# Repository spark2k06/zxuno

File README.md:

# loader128k y 128sna2rom

Cargador de "ROMs" para ZXUno a partir snapshots de 128K, para utilizar desde el menú del firmware. 

Por un lado tenemos el cargador loader128k, que se autocopia en la VRAM para despues pasar el control al mismo. 

Desde la VRAM se mueven todos los bloques de 16Kb al lugar que les corresponde, se restauran los registros y por último se 

pasa el control al PC del Snapshot.

128sna2rom por su parte se utiliza para crear la "ROM" parcheando datos de loader128k.

Idea desarrollada a partir del siguiente hilo con ayuda de Antonio Villena y el emulador ZEsarUX de Cesar Hernández:

http://www.zxuno.com/forum/viewtopic.php?f=12&t=530

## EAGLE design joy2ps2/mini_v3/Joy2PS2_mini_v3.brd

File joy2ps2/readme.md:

# JOY2PS2 Release 7

[Documentación en Español](https://dokuwiki.aitorgomez.net/joy2ps2_es)

[Documentation in English](https://dokuwiki.aitorgomez.net/joy2ps2_en)

## Release 1 Demo

## Development and history of the project

http://www.zxuno.com/forum/viewtopic.php?f=63&t=1508

http://www.zxuno.com/forum/viewtopic.php?f=63&t=1507

http://www.zxuno.com/forum/viewtopic.php?f=63&t=1500

http://www.zxuno.com/forum/viewtopic.php?f=63&t=796

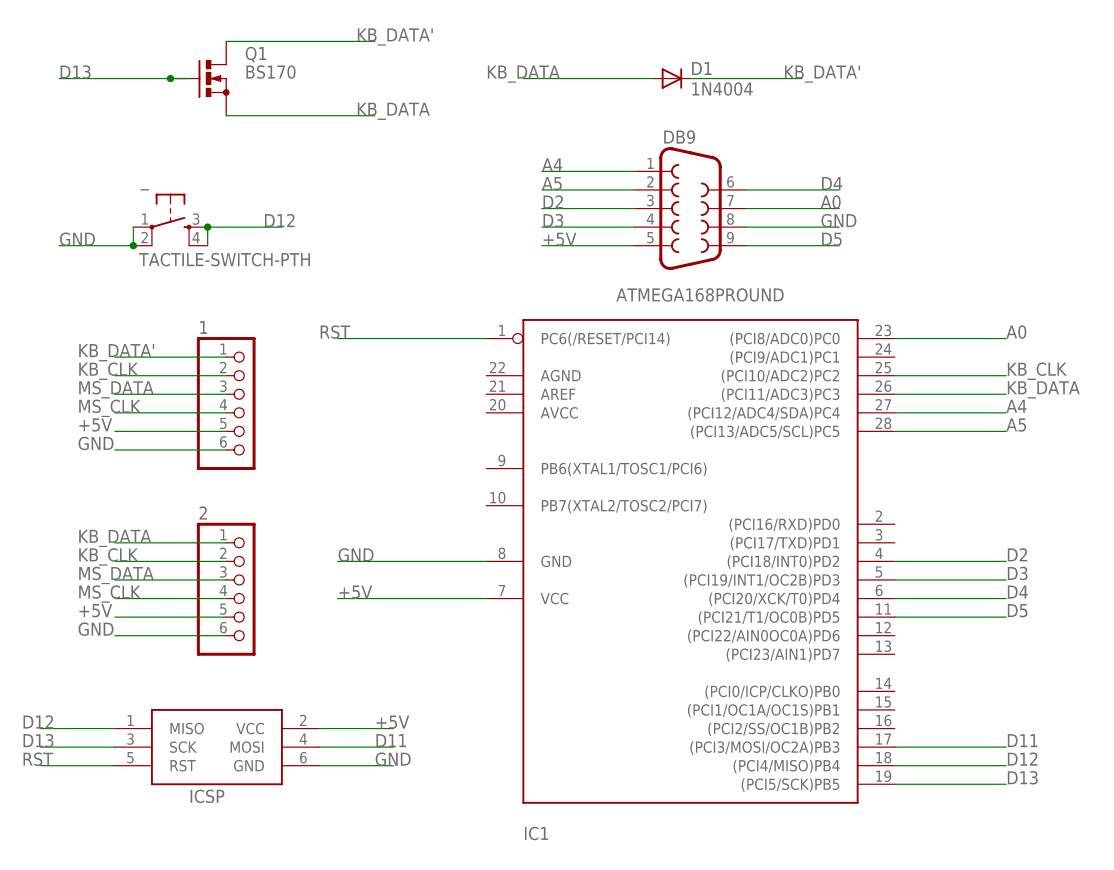
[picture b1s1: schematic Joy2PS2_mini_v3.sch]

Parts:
1, 2: PINHD-1X6; 1X06
D1: 1N4004; DO41-10
DB9: DB9MALE; DB9_MALE
IC1: ATMEGA168PROUND; DIL28-3-ROUND
ICSP: AVRISP-6; AVRISP
Q1: BS170; SOT54E
_: TACTILE-SWITCH-PTH; TAC-SWITCH-PTH

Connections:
+5V: 1.5, 2.5, DB9.5, IC1.7 (VCC), ICSP.2 (VCC)
A0: DB9.7, IC1.23 ((PCI8/ADC0)PC0)
A4: DB9.1, IC1.27 ((PCI12/ADC4/SDA)PC4)
A5: DB9.2, IC1.28 ((PCI13/ADC5/SCL)PC5)
D2: DB9.3, IC1.4 ((PCI18/INT0)PD2)
D3: DB9.4, IC1.5 ((PCI19/INT1/OC2B)PD3)
D4: DB9.6, IC1.6 ((PCI20/XCK/T0)PD4)
D5: DB9.9, IC1.11 ((PCI21/T1/OC0B)PD5)
D11: IC1.17 ((PCI3/MOSI/OC2A)PB3), ICSP.4 (MOSI)
D12: IC1.18 ((PCI4/MISO)PB4), ICSP.1 (MISO), _.3, _.4
D13: IC1.19 ((PCI5/SCK)PB5), ICSP.3 (SCK), Q1.G
GND: 1.6, 2.6, DB9.8, IC1.8 (GND), ICSP.6 (GND), _.1, _.2
KB_CLK: 1.2, 2.2, IC1.25 ((PCI10/ADC2)PC2)
KB_DATA: 2.1, D1.A, IC1.26 ((PCI11/ADC3)PC3), Q1.S
KB_DATA': 1.1, D1.C, Q1.D
MS_CLK: 1.4, 2.4
MS_DATA: 1.3, 2.3
RST: IC1.1 (PC6(/RESET/PCI14)), ICSP.5 (RST)

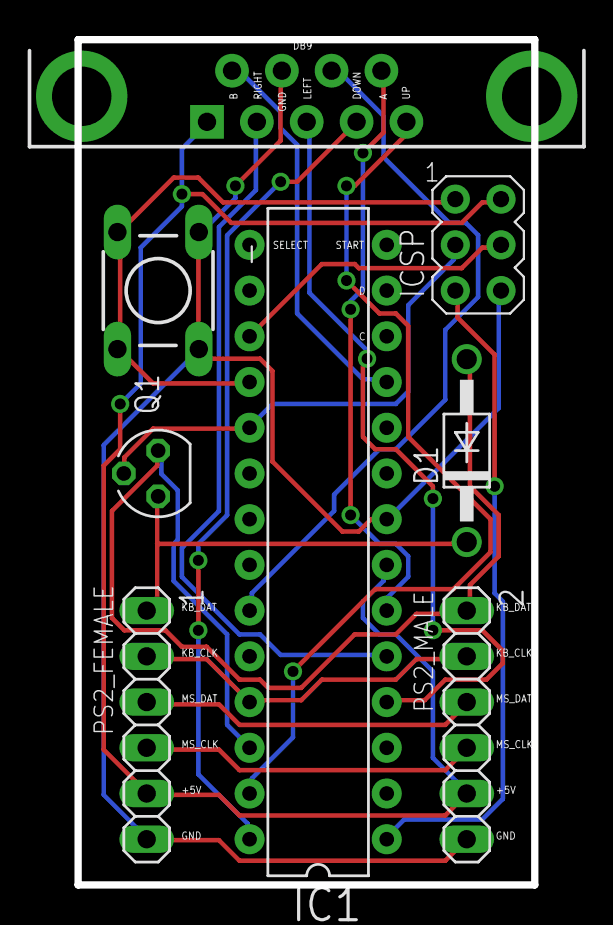
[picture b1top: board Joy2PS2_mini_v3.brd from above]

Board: 2 copper layers, 25.4 x 47.0 mm, 8 parts (0 on the bottom side), 18 nets.

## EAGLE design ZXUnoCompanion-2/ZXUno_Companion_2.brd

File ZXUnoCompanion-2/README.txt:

Lista BOM: http://spark2k06.info.tm/ZXUno_Companion_2_BOM.html
FAQ por Uto: http://uto.speccy.org/sugarlessfaq.html

http://www.zxuno.com/forum/viewtopic.php?f=63&t=1858
http://www.va-de-retro.com/foros/viewtopic.php?f=63&t=6551

Infografía de la configuracion de Jumpers por yoxxxoy:

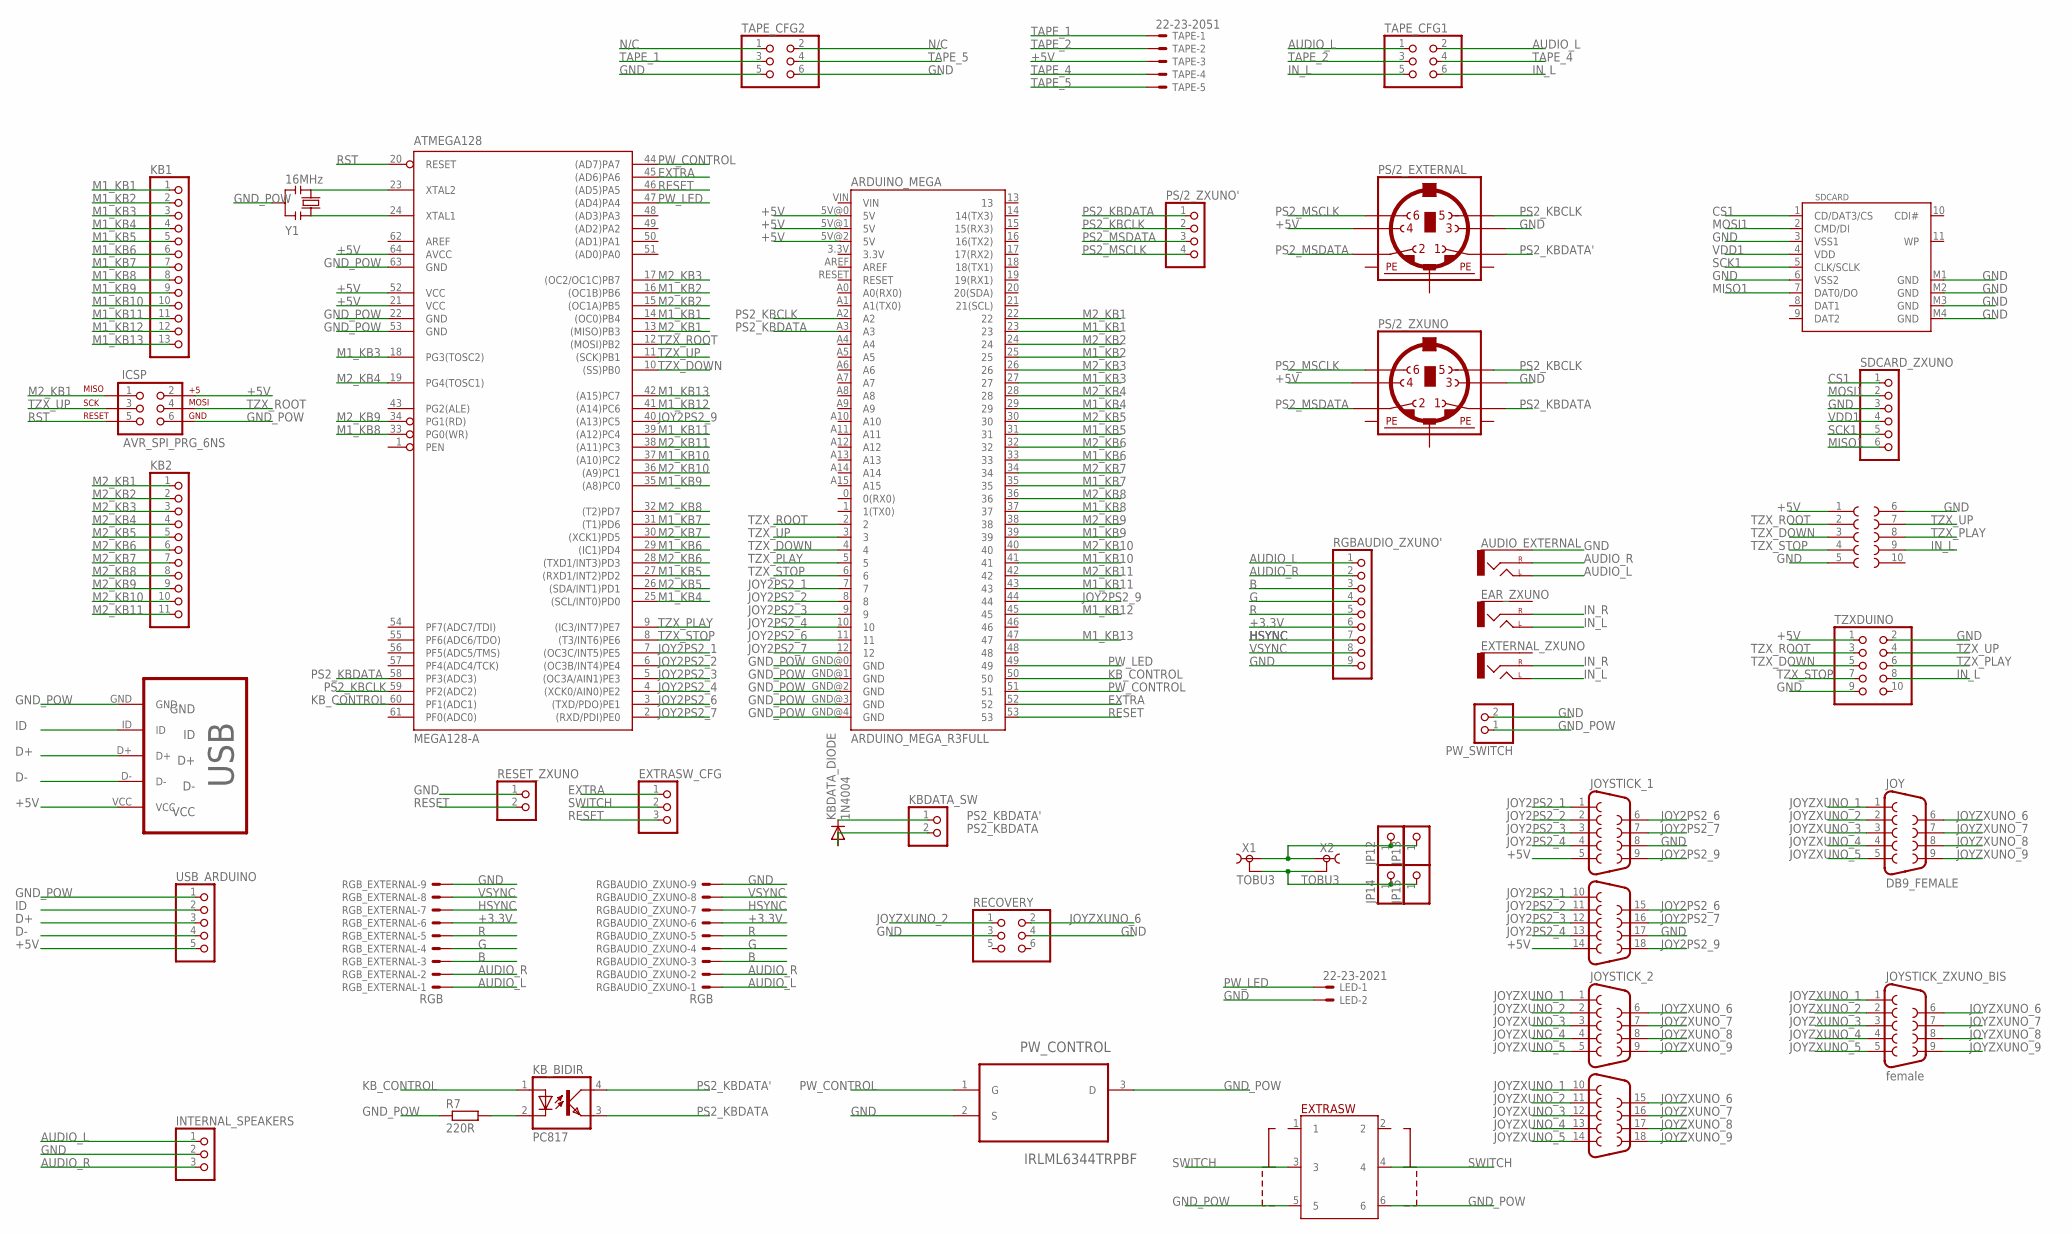
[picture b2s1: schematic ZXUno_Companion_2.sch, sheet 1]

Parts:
ARDUINO_MEGA: ARDUINO_MEGA_R3FULL; ARDUINO_MEGA
ATMEGA128: MEGA128-A; TQFP64
AUDIO_EXTERNAL: AUDIO-JACKPTH; AUDIO-JACK
EAR_ZXUNO: AUDIO-JACKPTH; AUDIO-JACK
EXTERNAL_ZXUNO: AUDIO-JACKPTH; AUDIO-JACK
EXTRASW: PS-22F03
EXTRASW_CFG: PINHD-1X3; 1X03
ICSP: AVR_SPI_PRG_6NS; 2X3-NS
INTERNAL_SPEAKERS: PINHD-1X3; 1X03
JOY: DB9_FEMALE; DB9
JOYSTICK_1, JOYSTICK_2: DB9MALE; DB9_MALE
JOYSTICK_ZXUNO_BIS: female; F09D
JP12, JP13, JP14, JP15: PINHD-1X1; 1X01
KB1: PINHD-1X13; 1X13
KB2: PINHD-1X11; 1X11
KBDATA_DIODE: 1N4004; DO41-10
KBDATA_SW: PINHD-1X2; 1X02
KB_BIDIR: PC817; DIL04
LED: 22-23-2021
PS/2_EXTERNAL, PS/2_ZXUNO: MINI_DIN_6; M_DIN6
PS/2_ZXUNO': PINHD-1X4; 1X04
PW_CONTROL: IRLML6344TRPBF; SOT95P240X112-3N
PW_SWITCH: PINHD-1X2; 1X02
R7: 220R; 0204/7
RECOVERY: PINHD-2X3; 2X03
RESET_ZXUNO: PINHD-1X2; 1X02
RGBAUDIO_ZXUNO: RGB; 53048-09
RGBAUDIO_ZXUNO': PINHD-1X9; 1X09
RGB_EXTERNAL: RGB; 53048-09
SDCARD: SDCARD; SDCMF-10915W010
SDCARD_ZXUNO: PINHD-1X6; 1X06
TAPE: 22-23-2051
TAPE_CFG1, TAPE_CFG2: PINHD-2X3; 2X03
TZXDUINO: PINHD-2X5; 2X05
U$1: MICRO-USB-B; MICRO_USB_4_LEGS
USB_ARDUINO: PINHD-1X5; 1X05
X1, X2: TOBU3
X5: F09D
Y1: 16MHz; RESONATOR

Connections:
+3.3V: RGBAUDIO_ZXUNO.6, RGBAUDIO_ZXUNO'.6, RGB_EXTERNAL.6; also elsewhere on the board
+5V: ARDUINO_MEGA.5V@1 (5V), ARDUINO_MEGA.5V@2 (5V), ATMEGA128.21 (VCC), ATMEGA128.52 (VCC), ATMEGA128.64 (AVCC), ICSP.2, JOYSTICK_1.5, JOYSTICK_1.14, PS/2_EXTERNAL.4, PS/2_ZXUNO.4, TAPE.3, TZXDUINO.1, U$1.VCC, USB_ARDUINO.5, X5.1; also elsewhere on the board
AUDIO_L: AUDIO_EXTERNAL.TIP (LEFT), INTERNAL_SPEAKERS.1, RGBAUDIO_ZXUNO.1, RGBAUDIO_ZXUNO'.1, RGB_EXTERNAL.1, TAPE_CFG1.1, TAPE_CFG1.2; also elsewhere on the board
AUDIO_R: AUDIO_EXTERNAL.RING (RIGHT), INTERNAL_SPEAKERS.3, RGBAUDIO_ZXUNO.2, RGBAUDIO_ZXUNO'.2, RGB_EXTERNAL.2; also elsewhere on the board
B: RGBAUDIO_ZXUNO.3, RGBAUDIO_ZXUNO'.3, RGB_EXTERNAL.3; also elsewhere on the board
CS1: SDCARD.1 (CD/DAT3/CS), SDCARD_ZXUNO.1
D+: U$1.D+, USB_ARDUINO.3
D-: U$1.D-, USB_ARDUINO.4
EXTRA: ARDUINO_MEGA.52, ATMEGA128.45 ((AD6)PA6), EXTRASW_CFG.1
G: RGBAUDIO_ZXUNO.4, RGBAUDIO_ZXUNO'.4, RGB_EXTERNAL.4; also elsewhere on the board
GND: AUDIO_EXTERNAL.SLEEVE, INTERNAL_SPEAKERS.2, JOYSTICK_1.8, JOYSTICK_1.17, LED.2, PS/2_EXTERNAL.3, PS/2_ZXUNO.3, PW_CONTROL.2 (S), PW_SWITCH.2, RECOVERY.3, RECOVERY.4, RESET_ZXUNO.1, RGBAUDIO_ZXUNO.9, RGBAUDIO_ZXUNO'.9, RGB_EXTERNAL.9, SDCARD.3 (VSS1), SDCARD.6 (VSS2), SDCARD.M1 (GND), SDCARD.M2 (GND), SDCARD.M3 (GND), SDCARD.M4 (GND), SDCARD_ZXUNO.3, TAPE_CFG2.5, TAPE_CFG2.6, TZXDUINO.2, TZXDUINO.9, X5.5, X5.6; also elsewhere on the board
GND_POW: ARDUINO_MEGA.GND@0 (GND), ARDUINO_MEGA.GND@1 (GND), ARDUINO_MEGA.GND@4 (GND), ATMEGA128.22 (GND), ATMEGA128.53 (GND), ATMEGA128.63 (GND), EXTRASW.5, EXTRASW.6, ICSP.6, PW_CONTROL.3 (D), PW_SWITCH.1, R7.1, U$1.GND, USB_ARDUINO.1, Y1.2
HSYNC: RGBAUDIO_ZXUNO.7, RGBAUDIO_ZXUNO'.7, RGB_EXTERNAL.7; also elsewhere on the board
ID: U$1.ID, USB_ARDUINO.2
IN_L: EAR_ZXUNO.TIP (LEFT), EXTERNAL_ZXUNO.TIP (LEFT), TAPE_CFG1.5, TAPE_CFG1.6, TZXDUINO.8, X5.9
IN_R: EAR_ZXUNO.RING (RIGHT), EXTERNAL_ZXUNO.RING (RIGHT)
JOY2PS2_1: ARDUINO_MEGA.7, ATMEGA128.7 ((OC3C/INT5)PE5), JOYSTICK_1.1, JOYSTICK_1.10
JOY2PS2_2: ARDUINO_MEGA.8, ATMEGA128.6 ((OC3B/INT4)PE4), JOYSTICK_1.2, JOYSTICK_1.11
JOY2PS2_3: ARDUINO_MEGA.9, ATMEGA128.5 ((OC3A/AIN1)PE3), JOYSTICK_1.3, JOYSTICK_1.12
JOY2PS2_4: ARDUINO_MEGA.10, ATMEGA128.4 ((XCK0/AIN0)PE2), JOYSTICK_1.4, JOYSTICK_1.13
JOY2PS2_6: ARDUINO_MEGA.11, ATMEGA128.3 ((TXD/PDO)PE1), JOYSTICK_1.6, JOYSTICK_1.15
JOY2PS2_7: ARDUINO_MEGA.12, ATMEGA128.2 ((RXD/PDI)PE0), JOYSTICK_1.7, JOYSTICK_1.16
JOY2PS2_9: ARDUINO_MEGA.44, ATMEGA128.40 ((A13)PC5), JOYSTICK_1.9, JOYSTICK_1.18
JOYZXUNO_1: JOY.1, JOYSTICK_2.1, JOYSTICK_2.10, JOYSTICK_ZXUNO_BIS.1
JOYZXUNO_2: JOY.2, JOYSTICK_2.2, JOYSTICK_2.11, JOYSTICK_ZXUNO_BIS.2, RECOVERY.1
JOYZXUNO_3: JOY.3, JOYSTICK_2.3, JOYSTICK_2.12, JOYSTICK_ZXUNO_BIS.3
JOYZXUNO_4: JOY.4, JOYSTICK_2.4, JOYSTICK_2.13, JOYSTICK_ZXUNO_BIS.4
JOYZXUNO_5: JOY.5, JOYSTICK_2.5, JOYSTICK_2.14, JOYSTICK_ZXUNO_BIS.5
JOYZXUNO_6: JOY.6, JOYSTICK_2.6, JOYSTICK_2.15, JOYSTICK_ZXUNO_BIS.6, RECOVERY.2
JOYZXUNO_7: JOY.7, JOYSTICK_2.7, JOYSTICK_2.16, JOYSTICK_ZXUNO_BIS.7
JOYZXUNO_8: JOY.8, JOYSTICK_2.8, JOYSTICK_2.17, JOYSTICK_ZXUNO_BIS.8
JOYZXUNO_9: JOY.9, JOYSTICK_2.9, JOYSTICK_2.18, JOYSTICK_ZXUNO_BIS.9
KB_CONTROL: ARDUINO_MEGA.50, ATMEGA128.60 (PF1(ADC1)), KB_BIDIR.1 (A)
M1_KB1: ARDUINO_MEGA.23, ATMEGA128.14 ((OC0)PB4), KB1.1
M1_KB2: ARDUINO_MEGA.25, ATMEGA128.16 ((OC1B)PB6), KB1.2
M1_KB3: ARDUINO_MEGA.27, ATMEGA128.18 (PG3(TOSC2)), KB1.3
M1_KB4: ARDUINO_MEGA.29, ATMEGA128.25 ((SCL/INT0)PD0), KB1.4
M1_KB5: ARDUINO_MEGA.31, ATMEGA128.27 ((RXD1/INT2)PD2), KB1.5
M1_KB6: ARDUINO_MEGA.33, ATMEGA128.29 ((IC1)PD4), KB1.6
M1_KB7: ARDUINO_MEGA.35, ATMEGA128.31 ((T1)PD6), KB1.7
M1_KB8: ARDUINO_MEGA.37, ATMEGA128.33 (PG0(WR)), KB1.8
M1_KB9: ARDUINO_MEGA.39, ATMEGA128.35 ((A8)PC0), KB1.9
M1_KB10: ARDUINO_MEGA.41, ATMEGA128.37 ((A10)PC2), KB1.10
M1_KB11: ARDUINO_MEGA.43, ATMEGA128.39 ((A12)PC4), KB1.11
M1_KB12: ARDUINO_MEGA.45, ATMEGA128.41 ((A14)PC6), KB1.12
M1_KB13: ARDUINO_MEGA.47, ATMEGA128.42 ((A15)PC7), KB1.13
M2_KB1: ARDUINO_MEGA.22, ATMEGA128.13 ((MISO)PB3), ICSP.1, KB2.1
M2_KB2: ARDUINO_MEGA.24, ATMEGA128.15 ((OC1A)PB5), KB2.2
M2_KB3: ARDUINO_MEGA.26, ATMEGA128.17 ((OC2/OC1C)PB7), KB2.3
M2_KB4: ARDUINO_MEGA.28, ATMEGA128.19 (PG4(TOSC1)), KB2.4
M2_KB5: ARDUINO_MEGA.30, ATMEGA128.26 ((SDA/INT1)PD1), KB2.5
M2_KB6: ARDUINO_MEGA.32, ATMEGA128.28 ((TXD1/INT3)PD3), KB2.6
M2_KB7: ARDUINO_MEGA.34, ATMEGA128.30 ((XCK1)PD5), KB2.7
M2_KB8: ARDUINO_MEGA.36, ATMEGA128.32 ((T2)PD7), KB2.8
M2_KB9: ARDUINO_MEGA.38, ATMEGA128.34 (PG1(RD)), KB2.9
M2_KB10: ARDUINO_MEGA.40, ATMEGA128.36 ((A9)PC1), KB2.10
M2_KB11: ARDUINO_MEGA.42, ATMEGA128.38 ((A11)PC3), KB2.11
MISO1: SDCARD.7 (DAT0/DO), SDCARD_ZXUNO.6
MOSI1: SDCARD.2 (CMD/DI), SDCARD_ZXUNO.2
unnamed: JP12.1, JP13.1, X1.1, X2.1
unnamed: JP14.1, JP15.1, X1.2, X1.2@1 (2), X1.2@2 (2), X2.2, X2.2@1 (2), X2.2@2 (2)
unnamed: KB_BIDIR.2 (C), R7.2
unnamed: ATMEGA128.23 (XTAL2), Y1.3
unnamed: ATMEGA128.24 (XTAL1), Y1.1
N/C: TAPE_CFG2.1, TAPE_CFG2.2
PE1: PS/2_EXTERNAL.SH1 (PE1), PS/2_ZXUNO.SH1 (PE1)
PE2: PS/2_EXTERNAL.SH2 (PE2), PS/2_ZXUNO.SH2 (PE2)
PE3: PS/2_EXTERNAL.SH3 (PE3), PS/2_ZXUNO.SH3 (PE3)
PS2_KBCLK: ARDUINO_MEGA.A2, ATMEGA128.59 (PF2(ADC2)), PS/2_EXTERNAL.5, PS/2_ZXUNO.5, PS/2_ZXUNO'.2
PS2_KBDATA: ARDUINO_MEGA.A3, ATMEGA128.58 (PF3(ADC3)), KBDATA_DIODE.A, KBDATA_SW.2, KB_BIDIR.3 (EMIT), PS/2_ZXUNO.1, PS/2_ZXUNO'.1
PS2_KBDATA': KBDATA_DIODE.C, KBDATA_SW.1, KB_BIDIR.4 (COL), PS/2_EXTERNAL.1
PS2_MSCLK: PS/2_EXTERNAL.6, PS/2_ZXUNO.6, PS/2_ZXUNO'.4
PS2_MSDATA: PS/2_EXTERNAL.2, PS/2_ZXUNO.2, PS/2_ZXUNO'.3
PW_CONTROL: ARDUINO_MEGA.51, ATMEGA128.44 ((AD7)PA7), PW_CONTROL.1 (G)
PW_LED: ARDUINO_MEGA.49, ATMEGA128.47 ((AD4)PA4), LED.1
R: RGBAUDIO_ZXUNO.5, RGBAUDIO_ZXUNO'.5, RGB_EXTERNAL.5; also elsewhere on the board
RESET: ARDUINO_MEGA.53, ATMEGA128.46 ((AD5)PA5), EXTRASW_CFG.3, RESET_ZXUNO.2
RST: ATMEGA128.20 (RESET), ICSP.5
SCK1: SDCARD.5 (CLK/SCLK), SDCARD_ZXUNO.5
SWITCH: EXTRASW.3, EXTRASW.4, EXTRASW_CFG.2
TAPE_1: TAPE.1, TAPE_CFG2.3
TAPE_2: TAPE.2, TAPE_CFG1.3
TAPE_4: TAPE.4, TAPE_CFG1.4
TAPE_5: TAPE.5, TAPE_CFG2.4
TZX_DOWN: ARDUINO_MEGA.4, ATMEGA128.10 ((SS)PB0), TZXDUINO.5, X5.3
TZX_PLAY: ARDUINO_MEGA.5, ATMEGA128.9 ((IC3/INT7)PE7), TZXDUINO.6, X5.8
TZX_ROOT: ARDUINO_MEGA.2, ATMEGA128.12 ((MOSI)PB2), ICSP.4, TZXDUINO.3, X5.2
TZX_STOP: ARDUINO_MEGA.6, ATMEGA128.8 ((T3/INT6)PE6), TZXDUINO.7, X5.4
TZX_UP: ARDUINO_MEGA.3, ATMEGA128.11 ((SCK)PB1), ICSP.3, TZXDUINO.4, X5.7
VDD1: SDCARD.4 (VDD), SDCARD_ZXUNO.4
VSYNC: RGBAUDIO_ZXUNO.8, RGBAUDIO_ZXUNO'.8, RGB_EXTERNAL.8; also elsewhere on the board

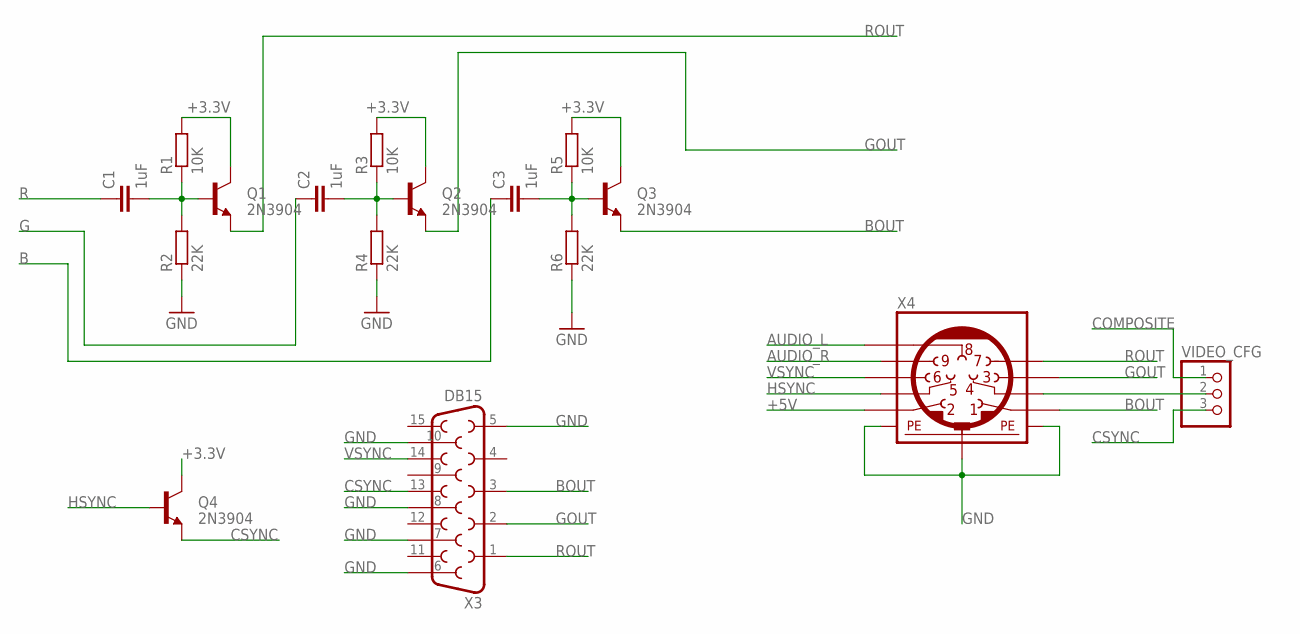
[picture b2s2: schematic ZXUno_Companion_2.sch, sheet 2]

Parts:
C1, C2, C3: 1uF; C050-035X075
Q1, Q2, Q3, Q4: 2N3904; TO-92
R1, R3, R5: 10K; 0204/7
R2, R4, R6: 22K; 0204/7
VIDEO_CFG: PINHD-1X3; 1X03
X3: DB15
X4: MINI_DIN_9; M_DIN9

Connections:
+3.3V: Q1.3 (C), Q2.3 (C), Q3.3 (C), Q4.3 (C), R1.2, R3.2, R5.2; also elsewhere on the board
+5V: X4.2; also elsewhere on the board
AUDIO_L: X4.8; also elsewhere on the board
AUDIO_R: X4.9; also elsewhere on the board
B: C3.1; also elsewhere on the board
BOUT: Q3.1 (E), X3.3, X4.1
COMPOSITE: VIDEO_CFG.1
CSYNC: Q4.1 (E), VIDEO_CFG.3, X3.13
G: C2.1; also elsewhere on the board
GND: R2.1, R4.1, R6.1, X3.5, X3.6, X3.7, X3.8, X3.10, X4.SH1 (PE1), X4.SH2 (PE2), X4.SH3 (PE3); also elsewhere on the board
GOUT: Q2.1 (E), X3.2, X4.3
HSYNC: Q4.2 (B), X4.5; also elsewhere on the board
unnamed: VIDEO_CFG.2, X4.4
unnamed: C1.2, Q1.2 (B), R1.1, R2.2
unnamed: C3.2, Q3.2 (B), R5.1, R6.2
unnamed: C2.2, Q2.2 (B), R3.1, R4.2
R: C1.1; also elsewhere on the board
ROUT: Q1.1 (E), X3.1, X4.7
VSYNC: X3.14, X4.6; also elsewhere on the board

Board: 2 copper layers, 62 parts (0 on the bottom side), 99 nets, no tracks yet.

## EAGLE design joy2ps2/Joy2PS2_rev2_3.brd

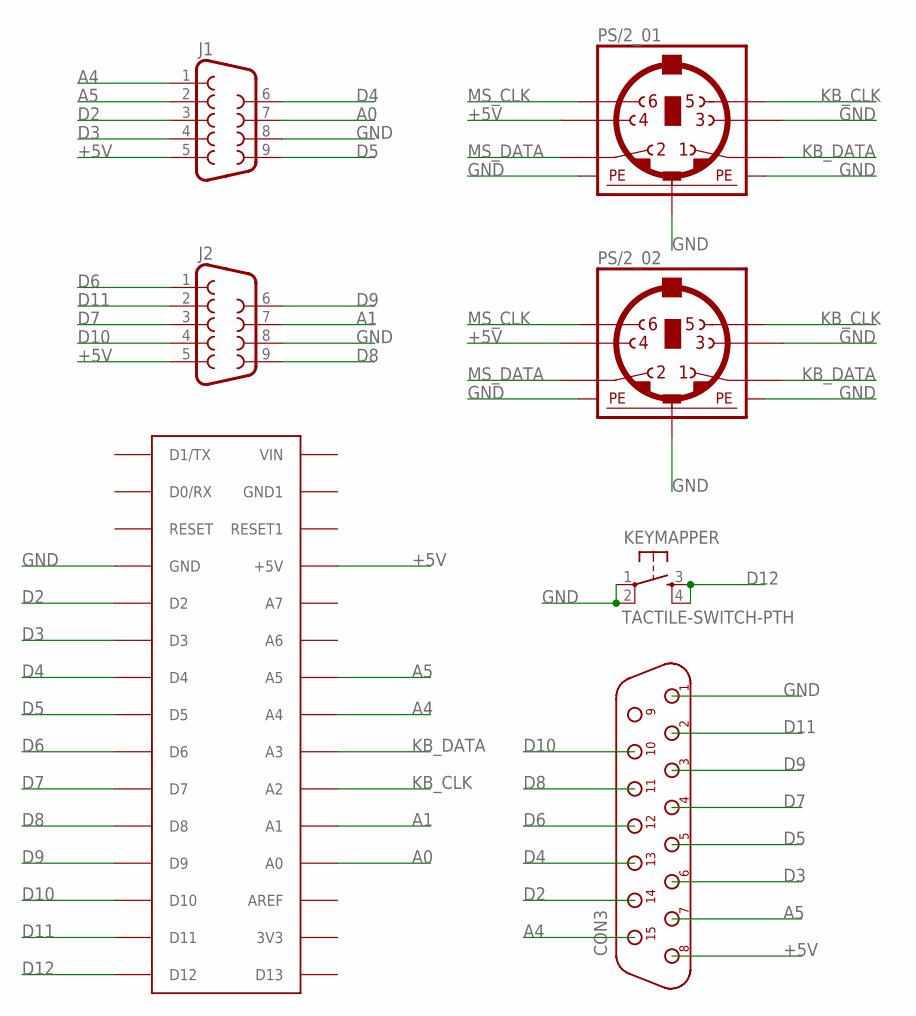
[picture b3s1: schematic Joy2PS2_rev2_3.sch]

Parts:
ARDUINONANO: ARDUINONANO; PDIP-32
CON3: DB15M/90; D-15M/90
J1, J2: DB9MALE; DB9_MALE
KEYMAPPER: TACTILE-SWITCH-PTH; TAC-SWITCH-PTH
PS/2_01, PS/2_02: MINI_DIN_6; M_DIN6

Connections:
+5V: ARDUINONANO.+5V, CON3.8, J1.5, J2.5, PS/2_01.4, PS/2_02.4
A0: ARDUINONANO.A0, J1.7
A1: ARDUINONANO.A1, J2.7
A4: ARDUINONANO.A4, CON3.15, J1.1
A5: ARDUINONANO.A5, CON3.7, J1.2
D2: ARDUINONANO.D2, CON3.14, J1.3
D3: ARDUINONANO.D3, CON3.6, J1.4
D4: ARDUINONANO.D4, CON3.13, J1.6
D5: ARDUINONANO.D5, CON3.5, J1.9
D6: ARDUINONANO.D6, CON3.12, J2.1
D7: ARDUINONANO.D7, CON3.4, J2.3
D8: ARDUINONANO.D8, CON3.11, J2.9
D9: ARDUINONANO.D9, CON3.3, J2.6
D10: ARDUINONANO.D10, CON3.10, J2.4
D11: ARDUINONANO.D11, CON3.2, J2.2
D12: ARDUINONANO.D12, KEYMAPPER.3, KEYMAPPER.4
GND: ARDUINONANO.GND, CON3.1, J1.8, J2.8, KEYMAPPER.1, KEYMAPPER.2, PS/2_01.3, PS/2_01.SH1 (PE1), PS/2_01.SH2 (PE2), PS/2_01.SH3 (PE3), PS/2_02.3, PS/2_02.SH1 (PE1), PS/2_02.SH2 (PE2), PS/2_02.SH3 (PE3)
KB_CLK: ARDUINONANO.A2, PS/2_01.5, PS/2_02.5
KB_DATA: ARDUINONANO.A3, PS/2_01.1, PS/2_02.1
MS_CLK: PS/2_01.6, PS/2_02.6
MS_DATA: PS/2_01.2, PS/2_02.2

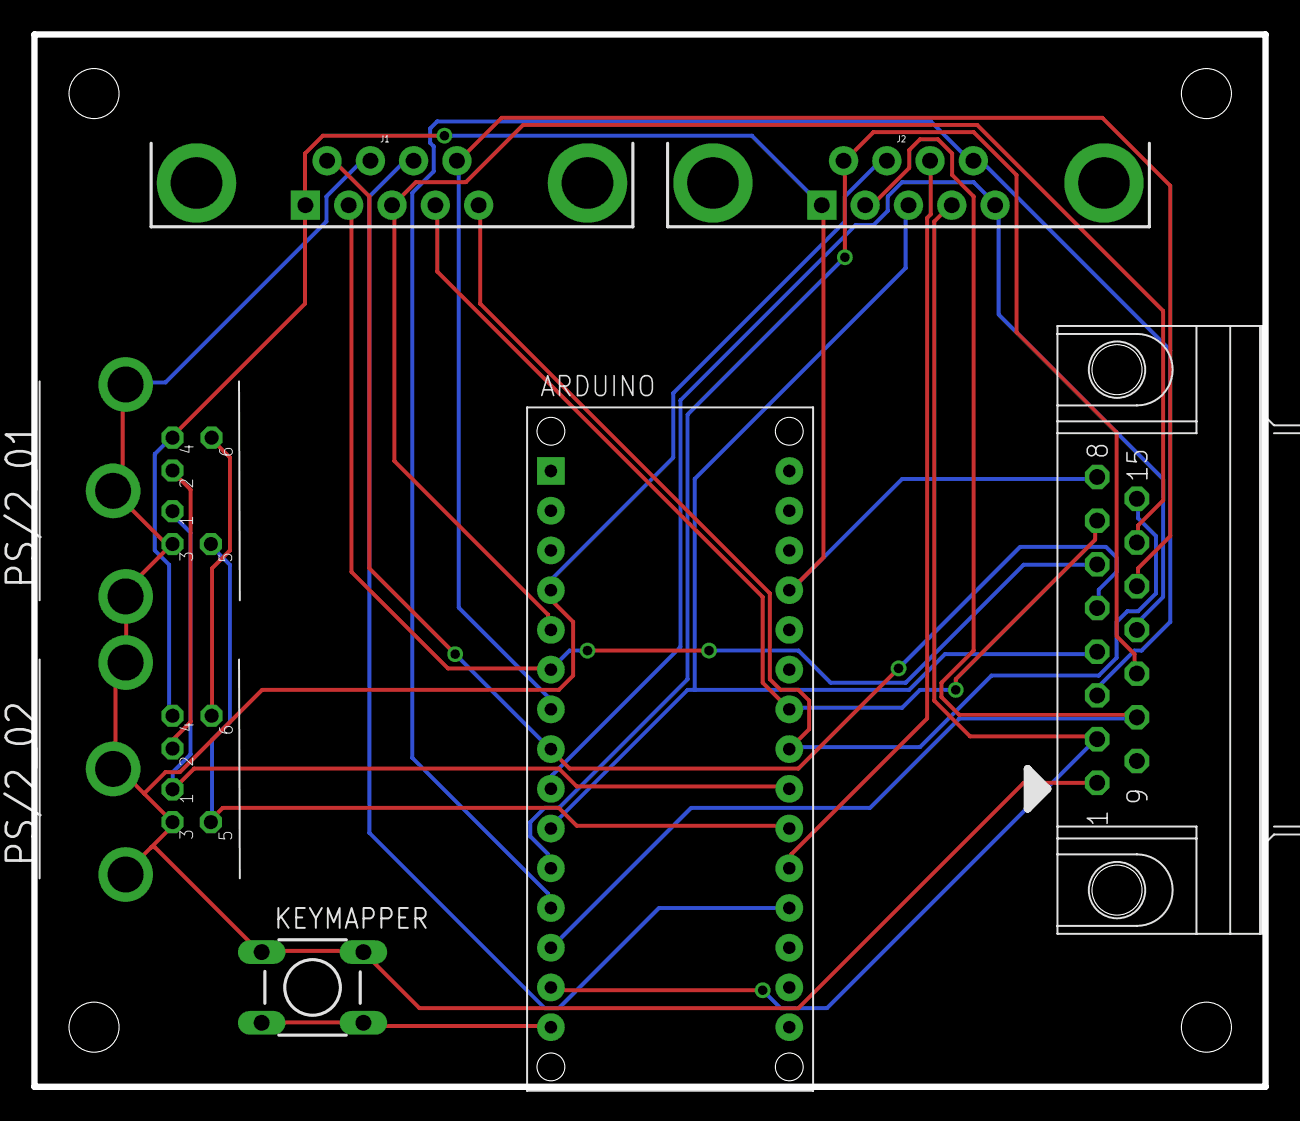
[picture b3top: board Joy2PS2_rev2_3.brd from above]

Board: 2 copper layers, 78.7 x 67.3 mm, 7 parts (0 on the bottom side), 21 nets.

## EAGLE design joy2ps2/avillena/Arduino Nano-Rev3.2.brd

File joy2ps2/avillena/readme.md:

# JOY2PS2

* Versión alternativa propuesta por Antonio Villena.

Código C para microcontroladores Atmega168/328 que permite mapear a scancodes de teclado PS/2 desde varios tipos de joysticks.

Por defecto, se encuentra configurado para poder utilizar el conector DB15, o bien el conector principal DB9. Esta configuración se puede cambiar en caliente mediante una combinación especial, de manera que se habilitaría el conector auxiliar DB9 y deshabilitaria el conector DB15. Esto es útil cuando se necesita jugar a dos jugadores con el mismo addon.

El conector DB15 admite por ahora los siguientes gamepads:

-> Neogeo Oldstyle

Los conectores db9 admiten por ahora los siguientes gamepads:

-> Atari DB9 1 o 2 botones
-> Megadrive de 3 o 6 botones, con botones Start y Select (Mode)
-> NES clonico, version de Antonio adaptado a Atari DB9

CONTROLES
---------

Desde el gamepad principal se puede controlar el ZXUno, así como todo tipo de menús. Al comienzo, éste siempre se encuentra mapeados en modo cursores, primer boton Enter y segundo Escape (modo menú tradicional).

En cualquier momento podremos pasar a un estado especial, al que llamaremos SHIFT. Para acceder a este estado, se puede hacer de cualquiera de las siguientes formas:

1. Pulsando Start + Boton 1
2. Pulsado Select + Start.
3. Pulsando y soltando la tecla Keymapper.

Una vez en el modo SHIFT, parecerá que no funciona ningún boton, pero no es asi. A partir de ahora se puede tomar la siguiente acción, que se llevará a cabo al pulsar el boton 1 del gamepad como evento final (para cancelar, volver a pulsar la combinacion de SHIFT, o bien pulsar el boton 2 del gamepad):

Nota: Las combinaciones abajo expuestas son pulsando y soltando (no mantener botones pulsados), cualquier cambio de direccion resetea el contador de las otras:

Sólo boton 1: Cambio de cursores a OPQA y viceversa en el joystick 1 (el principal)
Sólo boton 2: Cancelar modo SHIFT (también se puede cancelar volviendo a pulsar la combinación de SHIFT)

Opciones ABAJO
--------------

* 1 vez abajo y luego boton 1: NMI
* 2 veces abajo y luego boton 1: Reset (Se cambia automaticamente a cursores)
* 3 veces abajo y luego boton 1: MasterReset (Se cambia automaticamente a cursores)
* 4 veces abajo y luego boton 1: MasterReset y entrada a ROMs (Se cambia automaticamente a cursores)
* 5 veces abajo y luego boton 1: MasterReset y entrada a cores (Se cambia automaticamente a cursores)
* 6 veces abajo y luego boton 1: MasterReset y entrada a BIOS (Se cambia automaticamente a cursores)
* 7 veces y siguientes... se mantiene en la opcion de las 6 veces.

Opciones ARRIBA
---------------

* 1 vez arriba y luego boton 1: tecla '1'
* 2 veces arriba y luego boton 1: tecla '2'
* ...
* 9 veces arriba y luego boton 1: tecla '9'
* 10 veces arriba y luego boton 1: tecla '0'
* ... siguientes, se mantiene en la última opción '0'

Opciones DERECHA
----------------

* 1 vez y sucesivas: teclas 'J ""' (load modo 48k)

Opciones IZQUIERDA
------------------

* 1 vez izquierda y luego boton 1: Modo teclado completo (ver abajo)
* 2 veces izquierda y luego boton 1: Escape (necesario si se usa joystick de un solo boton, junto como el boton de keymapper a modo de shift)
* 3 veces izquierda y luego boton 1 de jugador 1 o 2: Cambio de mapa del jugador correspondiente. (ver abajo mapas disponibles)
* 4 veces izquierda y luego boton 1: Tecla Extend
* 5 veces izquierda y luego boton 1: Tecla Caps (LCTRL)
* 6 veces izquierda y luego boton 1: Tecla Symbol (RCTRL)
* 7 veces izquierda y luego boton 1: Tecla Graph (RALT)
* 8 veces izquierda y luego boton 1: Tecla TrueVid (F3)
* 9 veces izquierda y luego boton 1: Tecla InvVid (F4)
* 10 veces y siguientes... se mantiene en la opcion 9.

CAMBIO ENTRE DB15/DB9 Y DB9x2
-----------------------------

* Estando en modo SHIFT pulsar el boton 1, y manteniendolo pulsado, pulsar boton 2.

(La configuración seleccionada permanece durante reseteos en caliente de ZXUno)

MODO TECLADO (KEYSTROKES)
-------------------------

* arriba: cambio de tecla hacia adelante e impresion en pantalla.
* abajo: cambio de tecla hacia atras e impresion en pantalla.
* izquierda: borrar tecla.
* derecha: aceptar tecla o espacio.
* boton 1: cambio de tecla a correspodiente con tecla derecha del shift (para imprimir mayusculas o caracteres especiales)
* boton 2: Enter

* Para salir: Entrar al modo SHIFT y elegir otra opción, o salir del modo SHIFT una vez dentro.

MAPAS DE TECLADO
----------------

El cambio de mapa es cíclico, después del último mapa vuelve el mapa 0.

Mapa 0 
------

(Por defecto al iniciar y resetear el ZXUno)

Jugador 1

	KEY_Q,       	// UP
	KEY_A,       	// DOWN
	KEY_O,       	// LEFT
	KEY_P,       	// RIGHT
	KEY_5,	      	// SELECT
	KEY_1,		// START
	KEY_SPACE, 	// BUTTON 1
	KEY_E,       	// BUTTON 2
	KEY_R,       	// BUTTON 3
	KEY_D,       	// BUTTON 4
	KEY_F,       	// BUTTON 5
	KEY_C        	// BUTTON 6

Jugador 2

	KEY_I,       	// UP
	KEY_K,       	// DOWN
	KEY_J,       	// LEFT
	KEY_L,       	// RIGHT
	KEY_6,	    	// SELECT
	KEY_2,		// START
	KEY_H,		// BUTTON 1
	KEY_G,       	// BUTTON 2
	KEY_N,       	// BUTTON 3
	KEY_B,       	// BUTTON 4
	KEY_Y,       	// BUTTON 5
	KEY_T        	// BUTTON 6

Mapa 1
------

Jugador 1

	KEY_W,       	// UP
	KEY_S,       	// DOWN
	KEY_A,       	// LEFT
	KEY_D,       	// RIGHT
	KEY_5,	     	// SELECT
	KEY_1,		// START
	KEY_F,		// BUTTON 1
	KEY_E,       	// BUTTON 2
	KEY_R,       	// BUTTON 3
	KEY_D,       	// BUTTON 4
	KEY_F,       	// BUTTON 5
	KEY_C        	// BUTTON 6

Jugador 2

	KEY_I,       	// UP
	KEY_K,       	// DOWN
	KEY_J,       	// LEFT
	KEY_L,       	// RIGHT
	KEY_6,	    	// SELECT
	KEY_2,		// START
	KEY_H,		// BUTTON 1
	KEY_G,       	// BUTTON 2
	KEY_N,       	// BUTTON 3
	KEY_B,       	// BUTTON 4
	KEY_Y,       	// BUTTON 5
	KEY_T        	// BUTTON 6

Mapa 2
------

(Teclas por defecto de M.A.M.E)

Jugador 1

	KEY_UP,       	// UP
	KEY_DOWN,      	// DOWN
	KEY_LEFT,      	// LEFT
	KEY_RIGHT,     	// RIGHT
	KEY_5,	      	// SELECT
	KEY_1,		// START
	KEY_LCTRL,    	// BUTTON 1
	KEY_LALT,       // BUTTON 2
	KEY_SPACE,      // BUTTON 3
	KEY_LSHIFT,     // BUTTON 4
	KEY_Z,        	// BUTTON 5
	KEY_X         	// BUTTON 6

Jugador 2

	KEY_R,       	// UP
	KEY_F,       	// DOWN
	KEY_D,       	// LEFT
	KEY_G,       	// RIGHT
	KEY_6,	    	// SELECT
	KEY_2,		// START
	KEY_A,		// BUTTON 1
	KEY_S,       	// BUTTON 2
	KEY_Q,       	// BUTTON 3
	KEY_W,       	// BUTTON 4
	KEY_E,       	// BUTTON 5 // Not set by default on MAME
	KEY_T        	// BUTTON 6 // Not set by default on MAME

TO DO LIST
----------

* Soporte de gamepads de tipo Famicom DB9
* Revisar compatibilidad con ordenadores PC con entrada de teclado PS/2. (Ahora no funciona bien)
* Posibilidad de inicialización de teclado. (Puede que sea necesario para PCs)
* Implementación y acceso al set 1 de scancodes. (Necesario para el core de PC/XT del ZXUno)

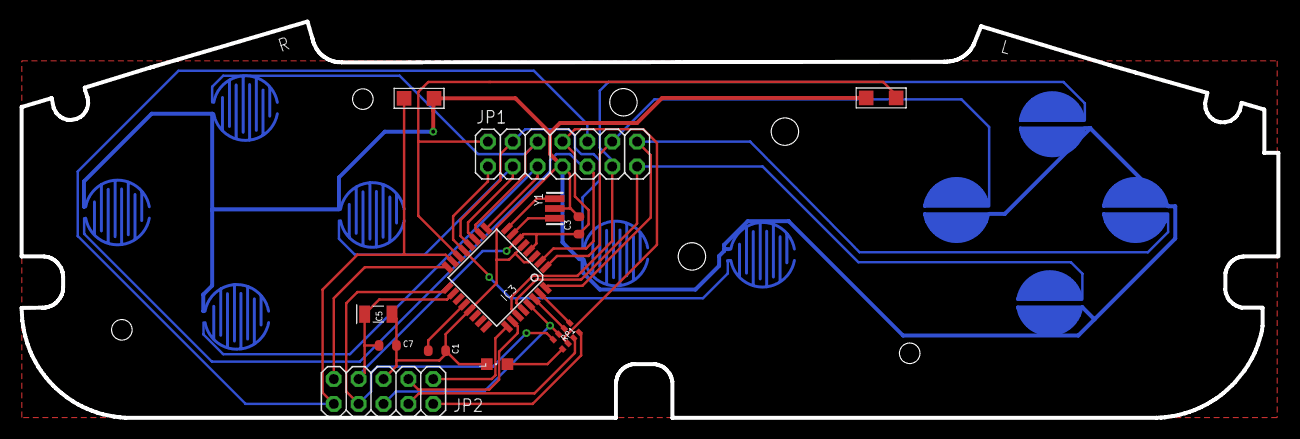
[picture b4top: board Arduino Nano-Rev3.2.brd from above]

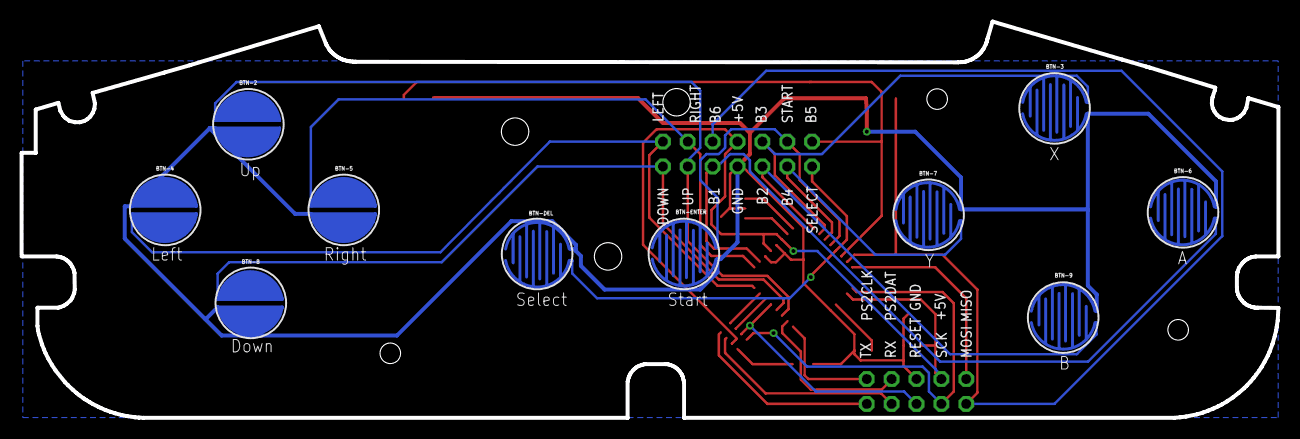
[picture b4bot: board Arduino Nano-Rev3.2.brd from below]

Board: 2 copper layers, 128.4 x 40.5 mm, 22 parts (10 on the bottom side), 27 nets.

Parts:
BTN-0: L; 1X02_SMD
BTN-1: R; 1X02_SMD
BTN-2: UP; BUTTON-CONDUCTIVE-PAD
BTN-3: X; BUTTON-CONDUCTIVE-BUTTON
BTN-4: LEFT; BUTTON-CONDUCTIVE-PAD
BTN-5: RIGHT; BUTTON-CONDUCTIVE-PAD
BTN-6: A; BUTTON-CONDUCTIVE-BUTTON
BTN-7: Y; BUTTON-CONDUCTIVE-BUTTON
BTN-8: DOWN; BUTTON-CONDUCTIVE-PAD
BTN-9: B; BUTTON-CONDUCTIVE-BUTTON
BTN-DEL: SELECT; BUTTON-CONDUCTIVE-BUTTON
BTN-ENTER: START; BUTTON-CONDUCTIVE-BUTTON
C1: 100nF; C0603-ROUND
C3, C7: 1uF; C0603-ROUND
C5: 4,7uF_16V; TAN-A
IC3: ATMEGA328P-AU; TQFP32-08
JP1: 2X07
JP2: 2X05
L: Yellow; CHIPLED_0805
RP1: 1K; CAY16
Y1: 16MHz; RESONATOR

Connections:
+5V: C3.1, C5.1, C7.1, IC3.4, IC3.6, IC3.18, JP1.8, JP2.7, RP1.6
A2: IC3.25, JP2.1
A3: IC3.26, JP2.3
A4: BTN-2.1, IC3.27, JP1.11
A5: BTN-8.1, IC3.28, JP1.13
AREF: C1.1, IC3.20
D0/RX: IC3.30, RP1.2
D1/TX: IC3.31, RP1.1
D2: BTN-4.2, IC3.32, JP1.14
D3: BTN-5.1, IC3.1, JP1.12
D4: BTN-6.1, IC3.2, JP1.9
D5: BTN-9.1, IC3.9, JP1.5
D6: BTN-3.2, IC3.10, JP1.6
D7: BTN-7.1, IC3.11, JP1.3
D8: BTN-ENTER.2, IC3.12, JP1.4
D9: BTN-DEL.1, IC3.13, JP1.1
D10: BTN-0.2, IC3.14, JP1.2
D11/MOSI: BTN-1.2, IC3.15, JP1.10, JP2.10
D12/MISO: IC3.16, JP2.9
D13/SCK: IC3.17, JP2.8, RP1.4
GND: BTN-0.1, BTN-1.1, BTN-2.2, BTN-3.1, BTN-4.1, BTN-5.2, BTN-6.2, BTN-7.2, BTN-8.2, BTN-9.2, BTN-DEL.2, BTN-ENTER.1, C1.2, C3.2, C5.2, C7.2, IC3.3, IC3.5, IC3.21, JP1.7, JP2.5, L.C, Y1.2
unnamed: IC3.8, Y1.3
unnamed: IC3.7, Y1.1
unnamed: L.A, RP1.5
RESET: IC3.29, JP2.6, RP1.3
RX: JP2.4, RP1.7
TX: JP2.2, RP1.8

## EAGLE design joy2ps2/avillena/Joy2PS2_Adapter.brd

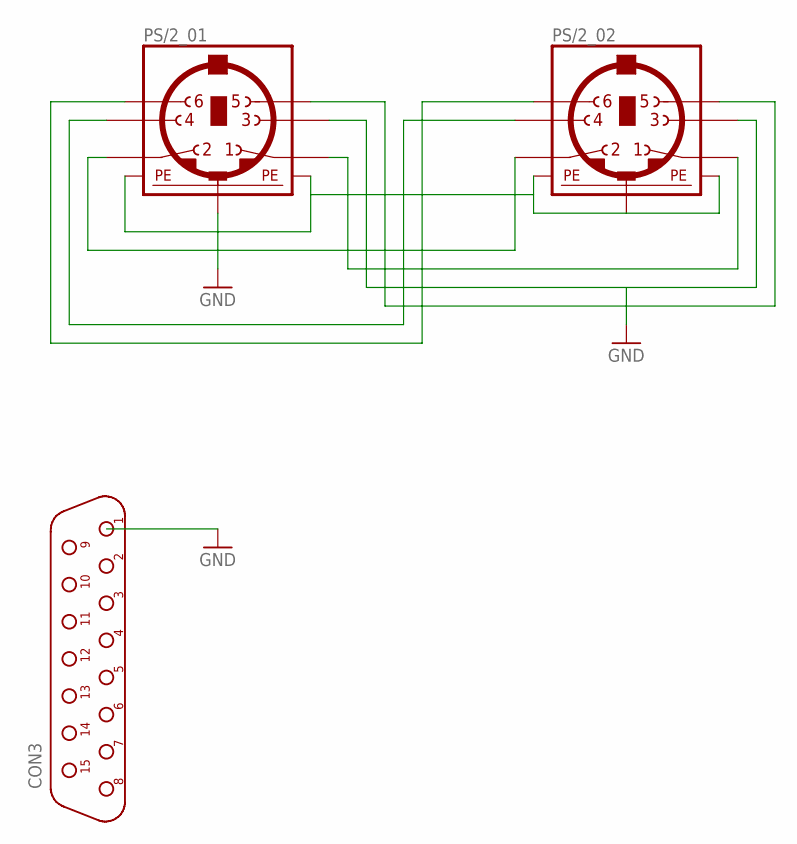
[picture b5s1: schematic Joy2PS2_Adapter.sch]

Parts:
CON3: DB15F/90; D-15F/90
PS/2_01, PS/2_02: MINI_DIN_6; M_DIN6

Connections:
GND: CON3.1, PS/2_01.3, PS/2_01.SH1 (PE1), PS/2_01.SH2 (PE2), PS/2_01.SH3 (PE3), PS/2_02.3, PS/2_02.SH1 (PE1), PS/2_02.SH2 (PE2), PS/2_02.SH3 (PE3)
unnamed: PS/2_01.1, PS/2_02.1
unnamed: PS/2_01.2, PS/2_02.2
unnamed: PS/2_01.4, PS/2_02.4
unnamed: PS/2_01.5, PS/2_02.5
unnamed: PS/2_01.6, PS/2_02.6

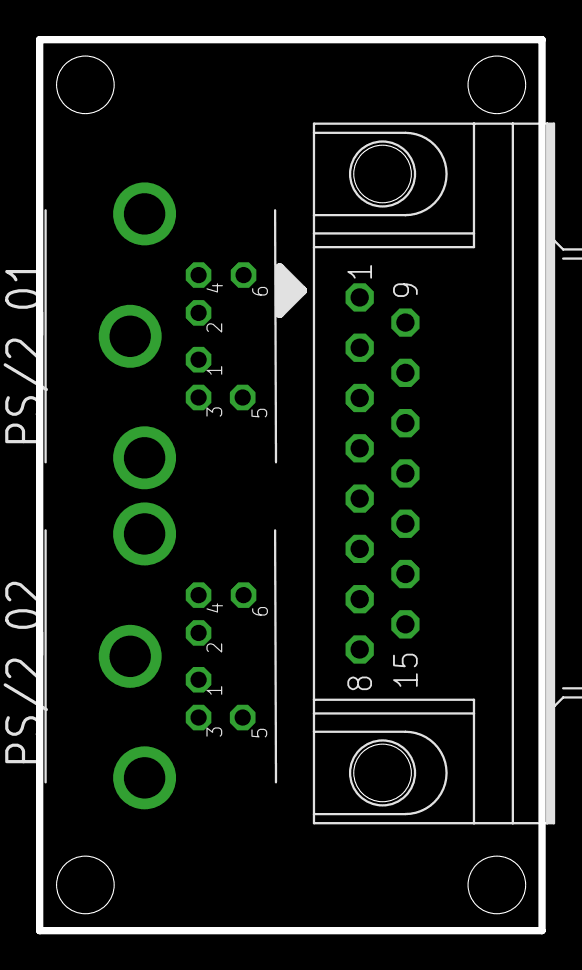
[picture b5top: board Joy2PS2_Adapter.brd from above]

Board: 2 copper layers, 27.9 x 49.5 mm, 3 parts (0 on the bottom side), 6 nets.

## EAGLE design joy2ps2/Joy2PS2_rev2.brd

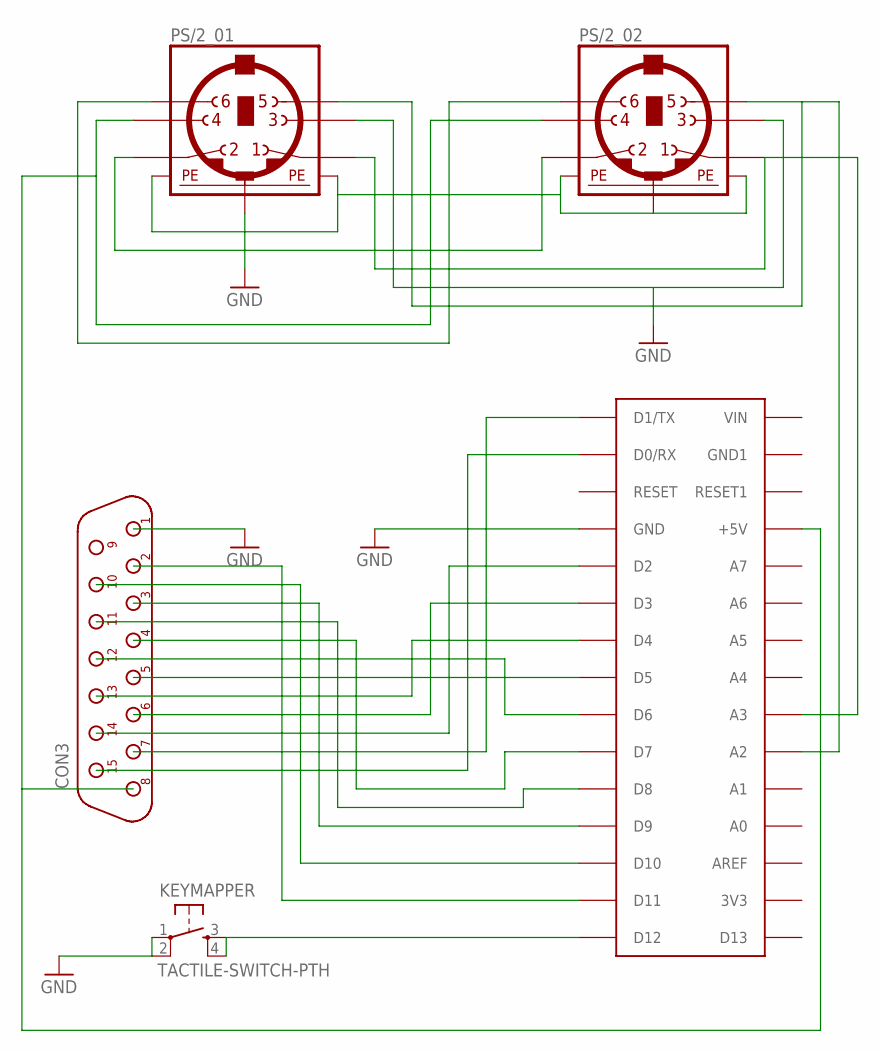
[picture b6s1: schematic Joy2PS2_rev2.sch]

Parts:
ARDUINONANO: ARDUINONANO; PDIP-32
CON3: DB15M/90; D-15M/90
KEYMAPPER: TACTILE-SWITCH-PTH; TAC-SWITCH-PTH
PS/2_01, PS/2_02: MINI_DIN_6; M_DIN6

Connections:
GND: ARDUINONANO.GND, CON3.1, KEYMAPPER.1, KEYMAPPER.2, PS/2_01.3, PS/2_01.SH1 (PE1), PS/2_01.SH2 (PE2), PS/2_01.SH3 (PE3), PS/2_02.3, PS/2_02.SH1 (PE1), PS/2_02.SH2 (PE2), PS/2_02.SH3 (PE3)
unnamed: ARDUINONANO.A3, PS/2_01.1, PS/2_02.1
unnamed: PS/2_01.2, PS/2_02.2
unnamed: ARDUINONANO.+5V, CON3.8, PS/2_01.4, PS/2_02.4
unnamed: ARDUINONANO.A2, PS/2_01.5, PS/2_02.5
unnamed: ARDUINONANO.D10, CON3.10
unnamed: ARDUINONANO.D8, CON3.11
unnamed: ARDUINONANO.D0/RX, CON3.15
unnamed: ARDUINONANO.D1/TX, CON3.7
unnamed: ARDUINONANO.D2, CON3.14
unnamed: ARDUINONANO.D3, CON3.6
unnamed: ARDUINONANO.D4, CON3.13
unnamed: ARDUINONANO.D5, CON3.5
unnamed: ARDUINONANO.D6, CON3.12
unnamed: ARDUINONANO.D7, CON3.4
unnamed: ARDUINONANO.D9, CON3.3
unnamed: ARDUINONANO.D11, CON3.2
unnamed: ARDUINONANO.D12, KEYMAPPER.3, KEYMAPPER.4
unnamed: PS/2_01.6, PS/2_02.6

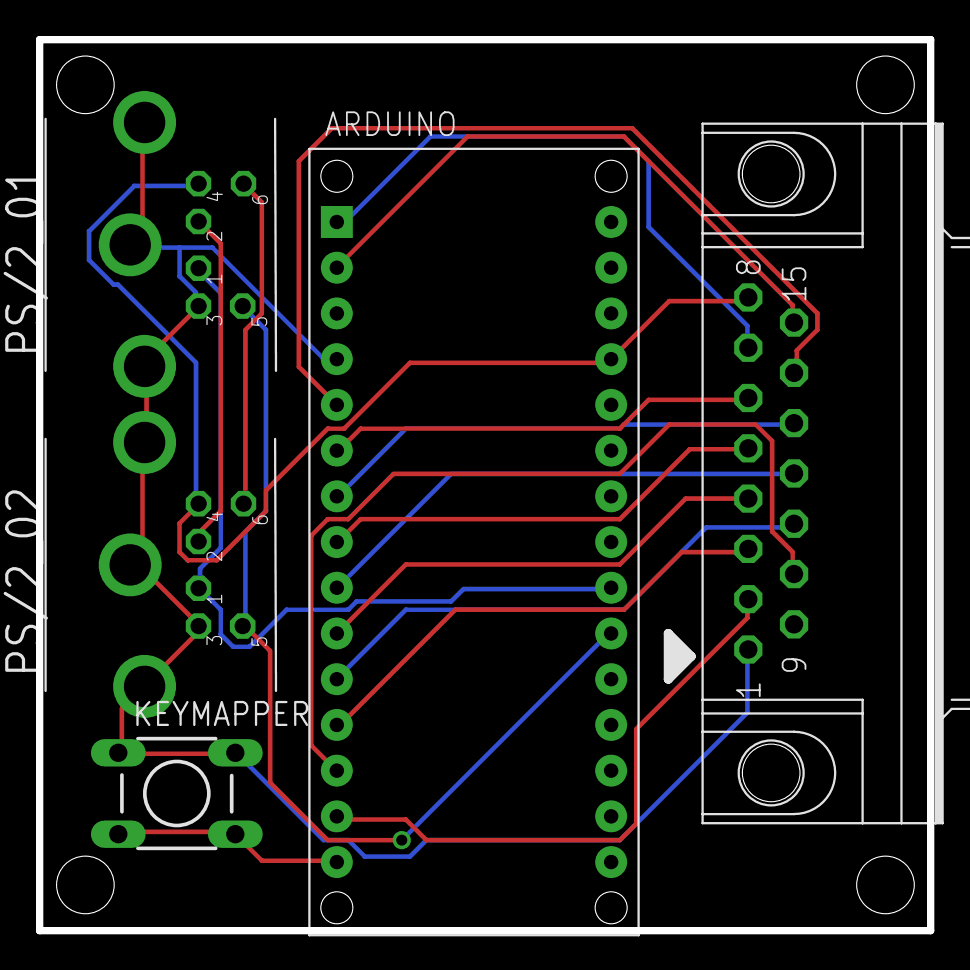
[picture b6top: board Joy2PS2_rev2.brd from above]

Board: 2 copper layers, 49.5 x 49.5 mm, 5 parts (0 on the bottom side), 19 nets.

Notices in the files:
parts and their libraries:
SparkFun-Connectors: Licensing: Creative Commons ShareAlike 4.0 International - https://creativecommons.org/licenses/by-sa/4.0
